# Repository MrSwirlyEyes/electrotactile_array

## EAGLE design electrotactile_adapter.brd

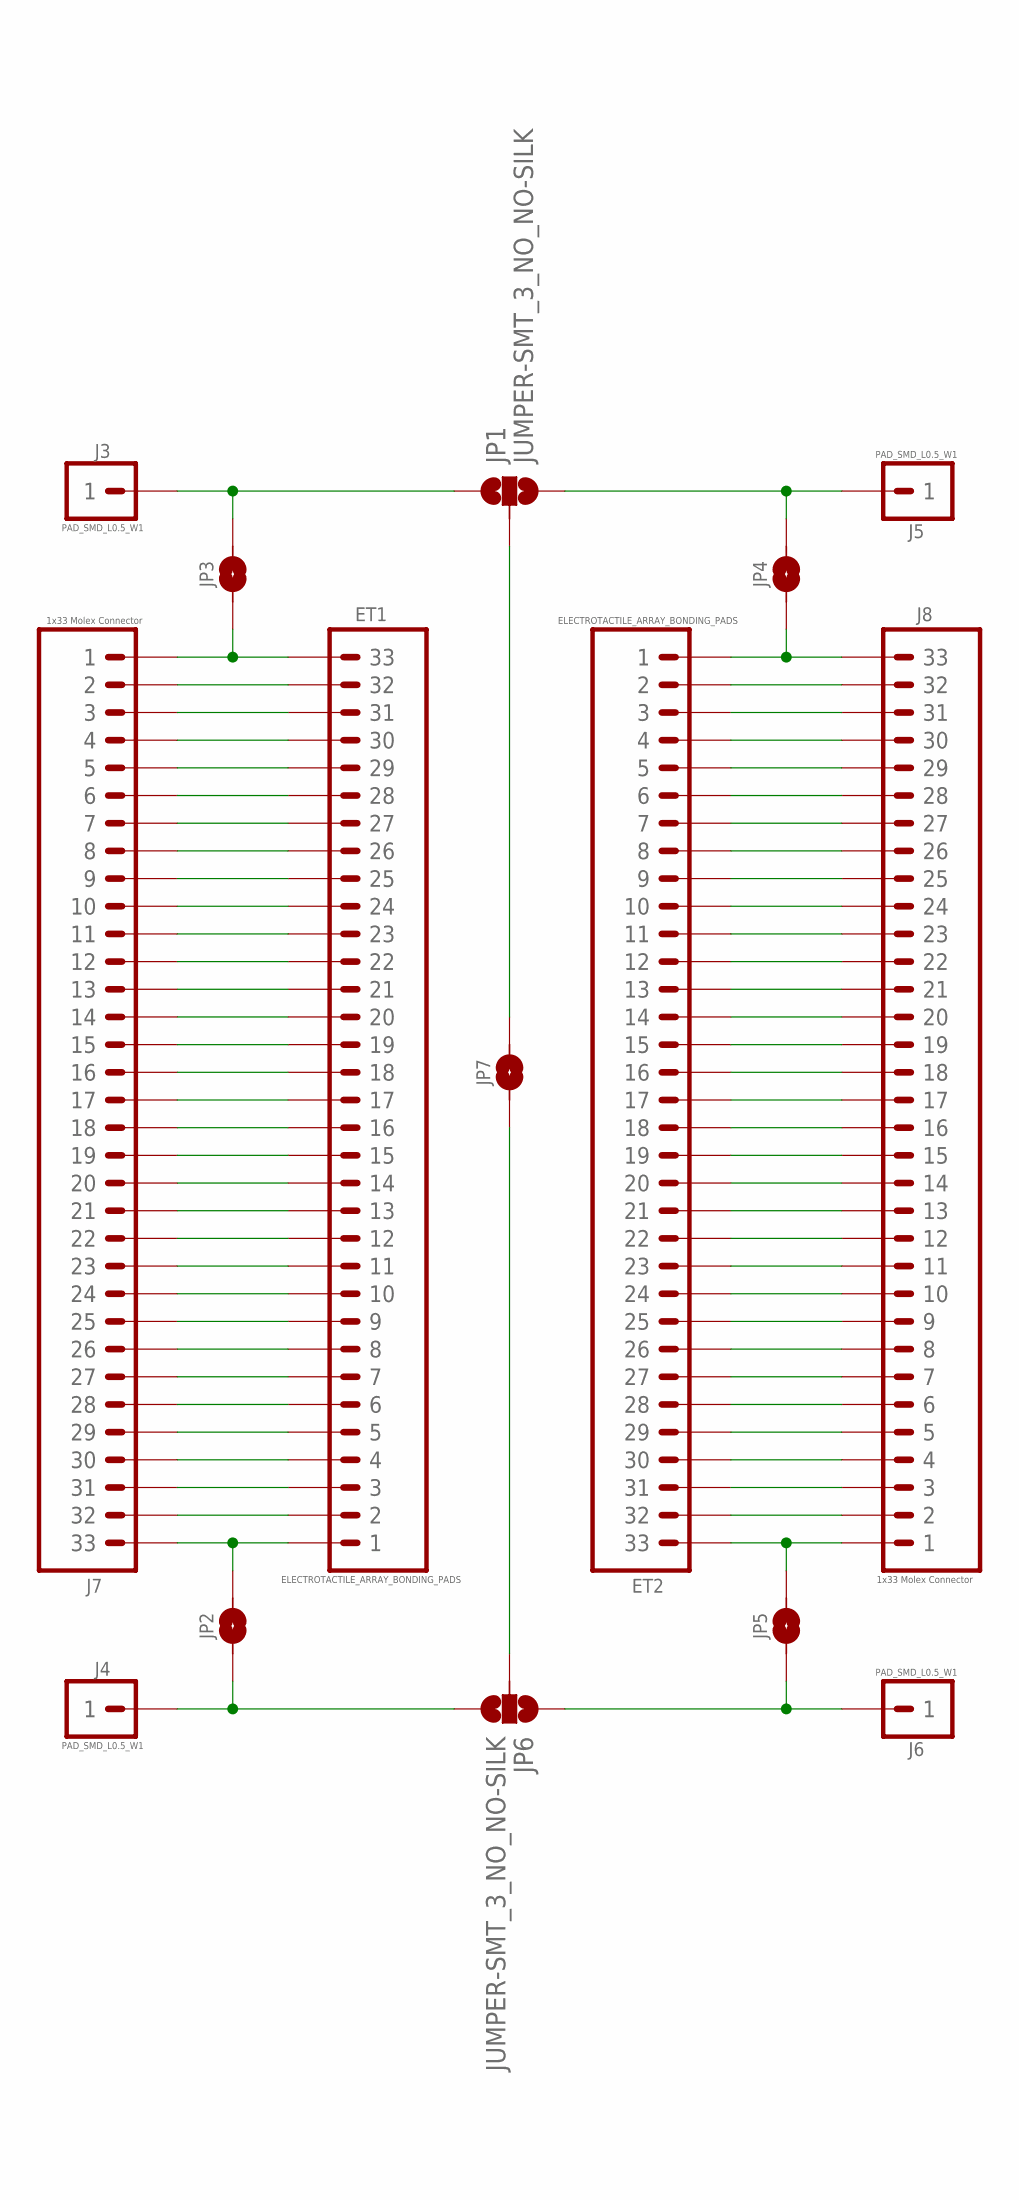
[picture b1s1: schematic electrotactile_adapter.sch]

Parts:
ET1, ET2: ELECTROTACTILE_ARRAY_BONDING_PADS
J3, J4, J5, J6: PAD_SMD_L0.5_W1; 1X01_SMD_L0.5-W1
J7, J8: 1x33 Molex Connector; _MOLEX-5025983393_FPC_PITCH-0.3MM
JP1, JP6: JUMPER-SMT_3_NO_NO-SILK; SMT-JUMPER_3_NO_NO-SILK
JP2, JP3, JP4, JP5, JP7: JUMPER_SMD_2-PAD_NO_SILK; SMT-JUMPER_2_NO_SILK

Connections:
unnamed: ET2.P$19 (19), J8.P$15 (15)
unnamed: ET2.P$2 (2), J8.P$32 (32)
unnamed: ET2.P$3 (3), J8.P$31 (31)
unnamed: ET2.P$4 (4), J8.P$30 (30)
unnamed: ET2.P$5 (5), J8.P$29 (29)
unnamed: ET2.P$6 (6), J8.P$28 (28)
unnamed: ET2.P$7 (7), J8.P$27 (27)
unnamed: ET2.P$8 (8), J8.P$26 (26)
unnamed: ET2.P$9 (9), J8.P$25 (25)
unnamed: ET2.P$10 (10), J8.P$24 (24)
unnamed: ET2.P$11 (11), J8.P$23 (23)
unnamed: ET2.P$12 (12), J8.P$22 (22)
unnamed: ET2.P$13 (13), J8.P$21 (21)
unnamed: ET2.P$1 (1), J8.P$33 (33), JP4.1
unnamed: ET2.P$14 (14), J8.P$20 (20)
unnamed: ET2.P$16 (16), J8.P$18 (18)
unnamed: ET2.P$17 (17), J8.P$17 (17)
unnamed: ET2.P$18 (18), J8.P$16 (16)
unnamed: ET2.P$15 (15), J8.P$19 (19)
unnamed: ET2.P$20 (20), J8.P$14 (14)
unnamed: ET2.P$21 (21), J8.P$13 (13)
unnamed: ET2.P$22 (22), J8.P$12 (12)
unnamed: ET2.P$24 (24), J8.P$10 (10)
unnamed: ET2.P$25 (25), J8.P$9 (9)
unnamed: ET2.P$26 (26), J8.P$8 (8)
unnamed: ET2.P$27 (27), J8.P$7 (7)
unnamed: ET2.P$28 (28), J8.P$6 (6)
unnamed: ET2.P$29 (29), J8.P$5 (5)
unnamed: ET2.P$30 (30), J8.P$4 (4)
unnamed: ET2.P$31 (31), J8.P$3 (3)
unnamed: ET2.P$32 (32), J8.P$2 (2)
unnamed: ET2.P$33 (33), J8.P$1 (1), JP5.2
unnamed: J5.P$1, JP1.3, JP4.2
unnamed: ET1.P$32 (32), J7.P$2 (2)
unnamed: ET1.P$31 (31), J7.P$3 (3)
unnamed: ET1.P$30 (30), J7.P$4 (4)
unnamed: ET1.P$29 (29), J7.P$5 (5)
unnamed: ET1.P$28 (28), J7.P$6 (6)
unnamed: ET1.P$27 (27), J7.P$7 (7)
unnamed: ET1.P$26 (26), J7.P$8 (8)
unnamed: ET1.P$25 (25), J7.P$9 (9)
unnamed: ET1.P$24 (24), J7.P$10 (10)
unnamed: ET1.P$23 (23), J7.P$11 (11)
unnamed: ET1.P$22 (22), J7.P$12 (12)
unnamed: ET1.P$21 (21), J7.P$13 (13)
unnamed: ET1.P$20 (20), J7.P$14 (14)
unnamed: ET1.P$1 (1), J7.P$33 (33), JP2.2
unnamed: ET1.P$19 (19), J7.P$15 (15)
unnamed: ET1.P$18 (18), J7.P$16 (16)
unnamed: ET1.P$17 (17), J7.P$17 (17)
unnamed: ET1.P$16 (16), J7.P$18 (18)
unnamed: ET1.P$15 (15), J7.P$19 (19)
unnamed: ET1.P$14 (14), J7.P$20 (20)
unnamed: ET1.P$13 (13), J7.P$21 (21)
unnamed: ET1.P$11 (11), J7.P$23 (23)
unnamed: ET1.P$12 (12), J7.P$22 (22)
unnamed: ET1.P$10 (10), J7.P$24 (24)
unnamed: ET1.P$9 (9), J7.P$25 (25)
unnamed: ET1.P$8 (8), J7.P$26 (26)
unnamed: ET1.P$7 (7), J7.P$27 (27)
unnamed: ET1.P$6 (6), J7.P$28 (28)
unnamed: ET1.P$5 (5), J7.P$29 (29)
unnamed: ET1.P$4 (4), J7.P$30 (30)
unnamed: ET1.P$3 (3), J7.P$31 (31)
unnamed: ET1.P$2 (2), J7.P$32 (32)
unnamed: ET1.P$33 (33), J7.P$1 (1), JP3.1
unnamed: J3.P$1, JP1.1, JP3.2
unnamed: J6.P$1, JP5.1, JP6.1
unnamed: J4.P$1, JP2.1, JP6.3
unnamed: JP6.2, JP7.1
unnamed: JP1.2, JP7.2
unnamed: ET2.P$23 (23), J8.P$11 (11)

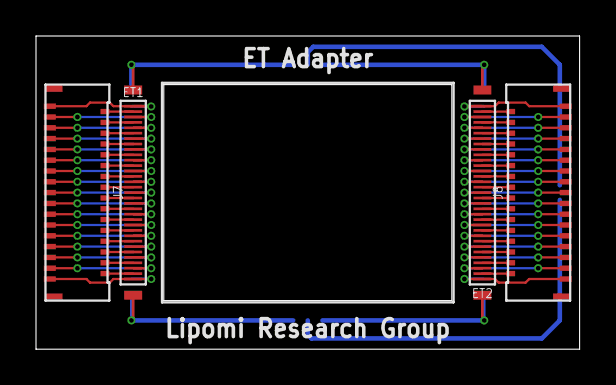
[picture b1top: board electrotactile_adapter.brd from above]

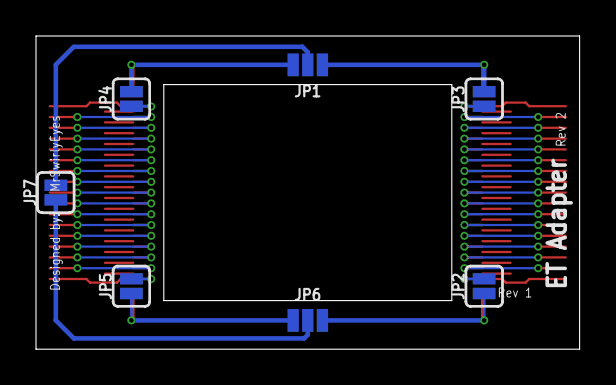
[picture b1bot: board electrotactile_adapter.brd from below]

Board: 4 copper layers, 30.2 x 17.4 mm, 16 parts (7 on the bottom side), 72 nets.

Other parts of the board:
U$1: ELECTROTACTILE_SUBSTRATE

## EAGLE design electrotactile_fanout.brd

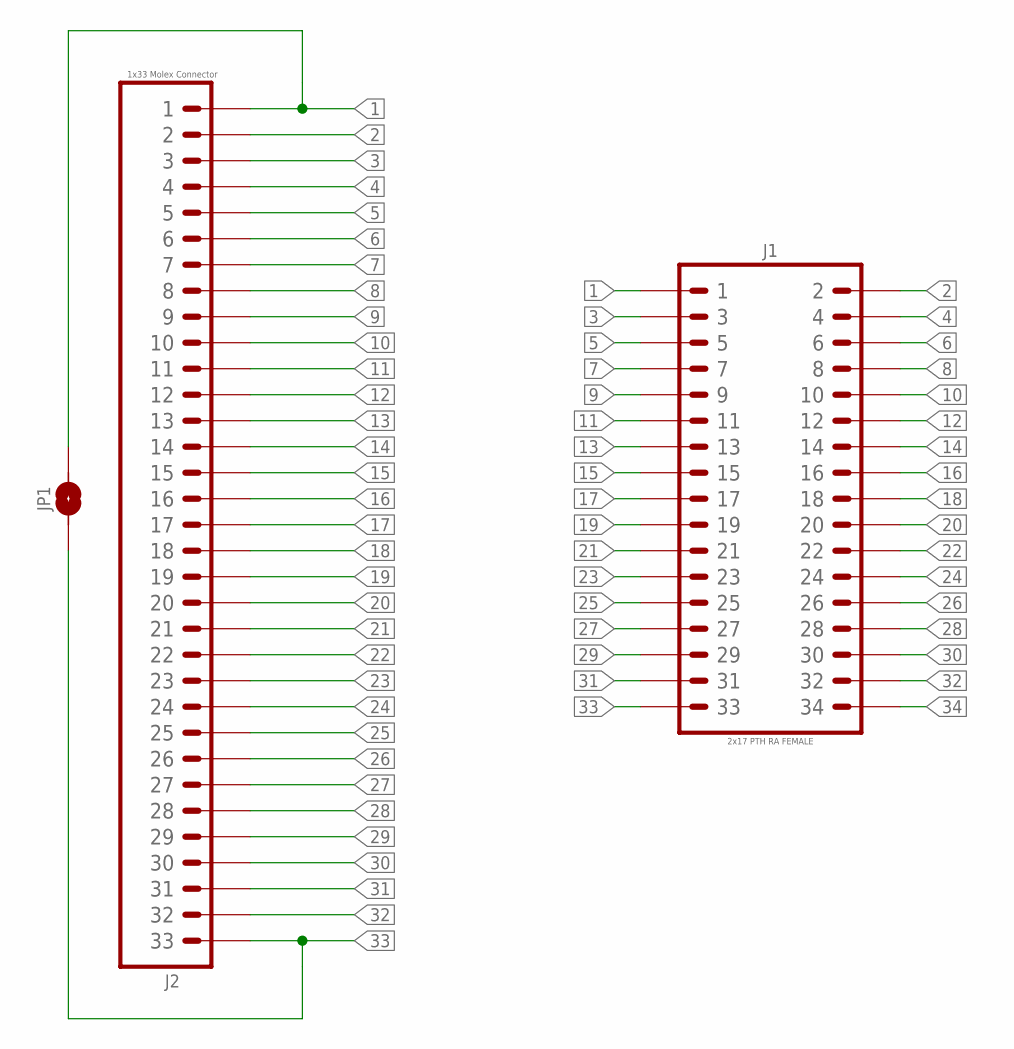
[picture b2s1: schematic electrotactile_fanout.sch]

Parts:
J1: 2x17 PTH RA FEMALE; 2X17-RA-FEMALE
J2: 1x33 Molex Connector; _MOLEX-5025983393_FPC_PITCH-0.3MM
JP1: JUMPER_SMD_2-PAD_NO_SILK; SMT-JUMPER_2_NO_SILK

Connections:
1: J1.1, J2.P$1 (1), JP1.2
2: J1.2, J2.P$2 (2)
3: J1.3, J2.P$3 (3)
4: J1.4, J2.P$4 (4)
5: J1.5, J2.P$5 (5)
6: J1.6, J2.P$6 (6)
7: J1.7, J2.P$7 (7)
8: J1.8, J2.P$8 (8)
9: J1.9, J2.P$9 (9)
10: J1.10, J2.P$10 (10)
11: J1.11, J2.P$11 (11)
12: J1.12, J2.P$12 (12)
13: J1.13, J2.P$13 (13)
14: J1.14, J2.P$14 (14)
15: J1.15, J2.P$15 (15)
16: J1.16, J2.P$16 (16)
17: J1.17, J2.P$17 (17)
18: J1.18, J2.P$18 (18)
19: J1.19, J2.P$19 (19)
20: J1.20, J2.P$20 (20)
21: J1.21, J2.P$21 (21)
22: J1.22, J2.P$22 (22)
23: J1.23, J2.P$23 (23)
24: J1.24, J2.P$24 (24)
25: J1.25, J2.P$25 (25)
26: J1.26, J2.P$26 (26)
27: J1.27, J2.P$27 (27)
28: J1.28, J2.P$28 (28)
29: J1.29, J2.P$29 (29)
30: J1.30, J2.P$30 (30)
31: J1.31, J2.P$31 (31)
32: J1.32, J2.P$32 (32)
33: J1.33, J2.P$33 (33), JP1.1
34: J1.34

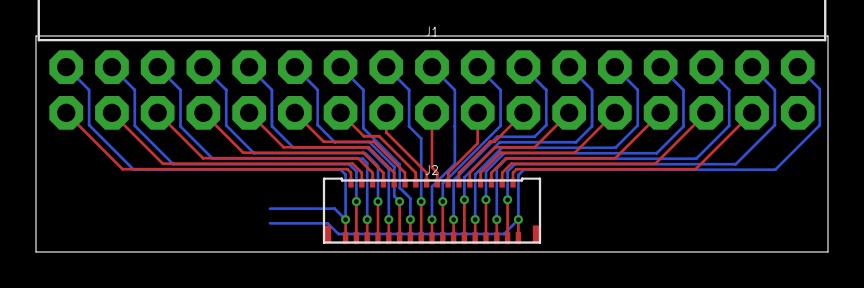
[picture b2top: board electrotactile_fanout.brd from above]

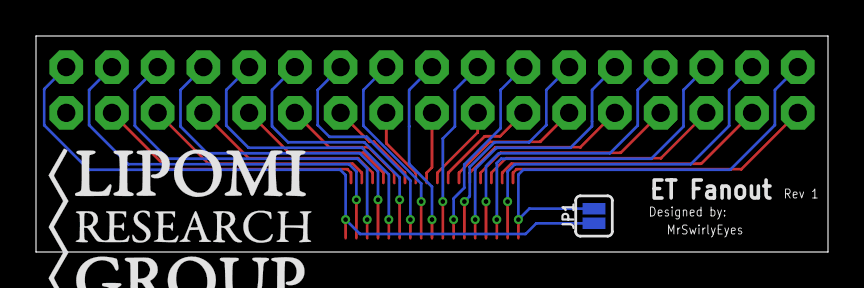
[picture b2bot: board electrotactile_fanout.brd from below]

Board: 2 copper layers, 44.0 x 12.0 mm, 4 parts (2 on the bottom side), 33 nets.

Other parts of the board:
U$1: LRG-LOGO

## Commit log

2018-07-06 Initialize repo with electrotactile adapter and fanout. Ready for fab.
2018-07-06 Update libraries with metadata.
2018-07-31 Update parts.
2018-08-28 Add 3D models.
2018-08-28 Add measure dimensions.
2018-08-29 Rev 2. Need to change size of ET cutout to 16mm x 12mm.
2018-10-06 update for Mickey.
2019-09-28 Update board.
